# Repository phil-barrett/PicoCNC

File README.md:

# PicoCNC

## Now fully open source
I have released the full V1.55eth design files under the MIT open source license. Please post your usage and derivations in the [Discussions Section](https://github.com/phil-barrett/PicoCNC/discussions).

## older readme.
No longer available for purchase.

A breakout board that, along with grblHAL and a Rapsberry Pi Pico microcontroller, creates a powerful CNC motion controller for devices like routers, mills, lasers and lathes.  Using grblHAL, it forms the basis of a motion control system with advanced features.

[System builder's Resources](https://www.grbl.org/resources)

[User Manual](https://github.com/phil-barrett/PicoCNC/blob/main/PicoCNC%20User%20Manual.pdf)

Key features of the PicoCNC board.
* Supports up to 4 Axes via Screw Terminal and Pin Header.
* Spindle control.
  - PWM (5V).
  - Direction (5V).
  - 0-10V.
  - 12V PWM supported (via open collector output).
* Limit Switches for each axis.
  - Supports switches or powered proximity sensors.​
  - 12V for better EMI immunity.
  - Separate power input for full isolation
  - Opto-isolated
* Relay support
  - Directly drive up to 7 relay coils via open collector outputs.​
  - Relay Coil voltage selectable between +5V or +12V.
  - Drive up to 11 SSR or Logic Level relays.
* Isolated standard Grbl input controls: Cycle Start, Feed Hold, EStop and Safety Door.​ Opto-Isolated.
* Opto-Isolated Probe input.
* Supports both Pico and Pico W.
* Comunications.
  - USB (via Pico and Pico W)
  - WiFi (via Pico W)
  - Ethernet (via Wiz850io Ethernet Module)
* Micro SD Card socket.  Allows storage of GCode programs.  GCode programs may be run from the SD Card.
* Dust Collection support.
  - Dust Collection relay and TTL output ganged to Spindle. 
  - Header for a switch to manually run Dust Collector.
* Flexible power input.  Two 12V sections, one for Stepper/Servo output, relays and spindle control, one for isolated limit, probe and control inputs. The two sections may be joined for the budget conscious builder. On board 5V generation.​
* LED indicators for 12V inputs, +5V​​ and spindle active.
* Open collector outputs allow adding pull-up resistors on the board.
* Expansion headers for I2C, SPI and UART.  UART 3.3V/5V translation supported.
* Powered by open source software - grblHAL.

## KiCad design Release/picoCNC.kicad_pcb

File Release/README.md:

## MIT License release of PicoCNC design files.

Copyright (c) 2023, 2025 Phillip L. Barrett

Permission is hereby granted, free of charge, to any person obtaining a copy
of this software and associated documentation files (the "Software"), to deal
in the Software without restriction, including without limitation the rights
to use, copy, modify, merge, publish, distribute, sublicense, and/or sell
copies of the Software, and to permit persons to whom the Software is
furnished to do so, subject to the following conditions:

The above copyright notice and this permission notice shall be included in all
copies or substantial portions of the Software.

THE SOFTWARE IS PROVIDED "AS IS", WITHOUT WARRANTY OF ANY KIND, EXPRESS OR
IMPLIED, INCLUDING BUT NOT LIMITED TO THE WARRANTIES OF MERCHANTABILITY,
FITNESS FOR A PARTICULAR PURPOSE AND NONINFRINGEMENT. IN NO EVENT SHALL THE
AUTHORS OR COPYRIGHT HOLDERS BE LIABLE FOR ANY CLAIM, DAMAGES OR OTHER
LIABILITY, WHETHER IN AN ACTION OF CONTRACT, TORT OR OTHERWISE, ARISING FROM,
OUT OF OR IN CONNECTION WITH THE SOFTWARE OR THE USE OR OTHER DEALINGS IN THE
SOFTWARE.

## Usage Notes

### KiCAD Files
These were created with KiCAD V8.0

They are released with the intent of using JLCPCB to manufacture the PCB and 
assemble them into a working circuit board. The directory production/ includes full gerbers (PicoU4XBB.zip), 
Bill of Materials including JLCPCB library part numbers (bom,.csv) and Centroid PnP (positions.csv).

### KiCAD plugins required
To create JLCPCB files after modifying the design, you will need the Fabrication Toolkit plugin. It is 
available in the KICAD Plugin and Content Manager.

### JLCPCB Library part numbers
These were current as of June 2025.  You may need to change due to out of stock parts.

## Questions, reports, suggestions

Please use the [Discussions section](https://github.com/phil-barrett/PicoCNC/discussions/34) to ask questions, report your progress or make suggestions.

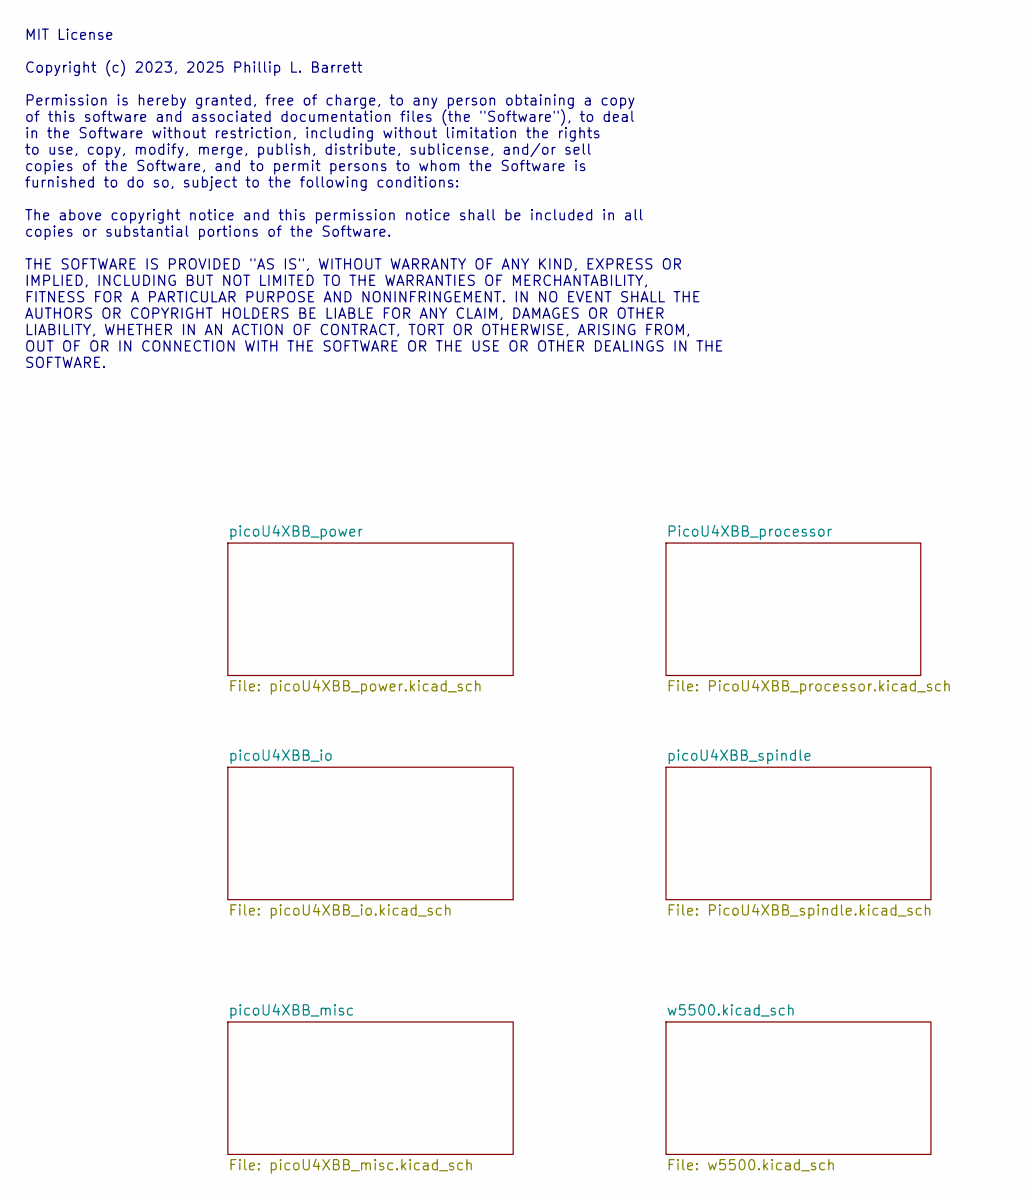
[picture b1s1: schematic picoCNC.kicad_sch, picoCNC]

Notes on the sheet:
MIT License Copyright (c) 2023, 2025 Phillip L. Barrett Permission is hereby granted, free of charge, to any person obtaining a copy of this software and associated documentation files (the "Software"), to deal in the Software without restriction, including without limitation the rights to use, cop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

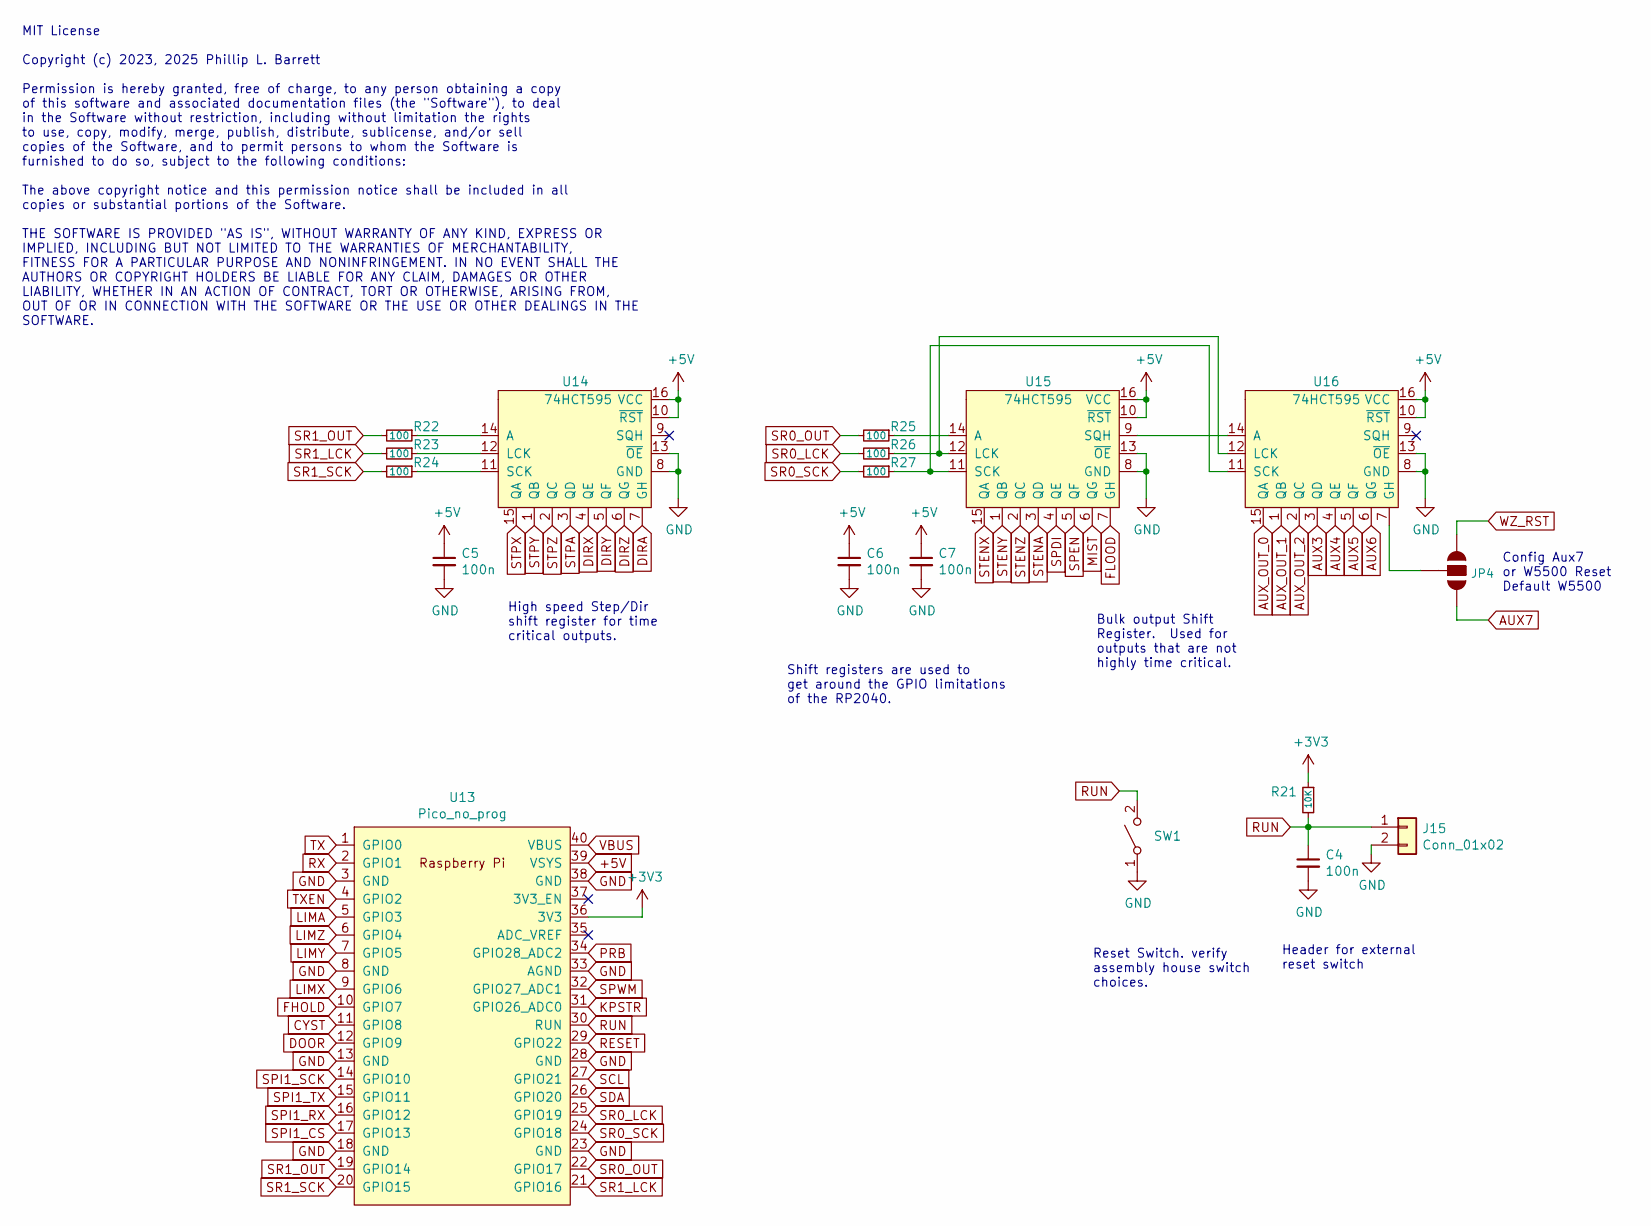
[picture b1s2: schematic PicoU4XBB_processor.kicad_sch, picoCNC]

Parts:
C4, C5, C6, C7: 100n; C_0805_2012Metric; LCSC C49678
J15: Conn_01x02; 1X02
JP4: JUMPER-SMT_3_NO_NO-SILK; SolderJumper-3_P1.3mm_Bridged12_Pad1.0x1.5mm
R21: 10K; R_0603_1608Metric; LCSC C25804
R22, R23, R24, R25, R26, R27: 100; R_0603_1608Metric; LCSC C22775
SW1: SW_SPST; TA-1088R-02026; LCSC C455280
U13: Pico_no_prog; RaspBerry_PI_Pico_no_prog
U14, U15, U16: 74HCT595; HTSSOP-16_4.4x5mm_P0.65; LCSC C460504

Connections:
+5V: C5.1, C6.1, C7.1, U13.39 (VSYS), U14.10 (~RST), U14.16 (VCC), U15.10 (~RST), U15.16 (VCC), U16.10 (~RST), U16.16 (VCC); also elsewhere on the board
AUX0: U16.15 (QA); also elsewhere on the board
AUX1: U16.1 (QB); also elsewhere on the board
AUX2: U16.2 (QC); also elsewhere on the board
AUX3: U16.3 (QD); also elsewhere on the board
AUX4: U16.4 (QE); also elsewhere on the board
AUX5: U16.5 (QF); also elsewhere on the board
AUX6: U16.6 (QG); also elsewhere on the board
AUX7: JP4.3; also elsewhere on the board
CYST: U13.11 (GPIO8); also elsewhere on the board
DIRA: U14.7 (GH); also elsewhere on the board
DIRX: U14.4 (QE); also elsewhere on the board
DIRY: U14.5 (QF); also elsewhere on the board
DIRZ: U14.6 (QG); also elsewhere on the board
DOOR: U13.12 (GPIO9); also elsewhere on the board
FHOLD: U13.10 (GPIO7); also elsewhere on the board
FLOOD: U15.7 (GH); also elsewhere on the board
GND: C4.2, C5.2, C6.2, C7.2, J15.2, SW1.1 (A), U13.3 (GND), U13.8 (GND), U13.13 (GND), U13.18 (GND), U13.23 (GND), U13.28 (GND), U13.33 (AGND), U13.38 (GND), U14.8 (GND), U14.13 (~OE), U15.8 (GND), U15.13 (~OE), U16.8 (GND), U16.13 (~OE); also elsewhere on the board
KPSTR: U13.31 (GPIO26_ADC0); also elsewhere on the board
LIMA: U13.5 (GPIO3); also elsewhere on the board
LIMX: U13.9 (GPIO6); also elsewhere on the board
LIMY: U13.7 (GPIO5); also elsewhere on the board
LIMZ: U13.6 (GPIO4); also elsewhere on the board
MIST: U15.6 (QG); also elsewhere on the board
unnamed: R22.1, U14.14 (A)
unnamed: R23.1, U14.12 (LCK)
unnamed: R24.1, U14.11 (SCK)
unnamed: R25.1, U15.14 (A)
unnamed: R26.1, U15.12 (LCK), U16.12 (LCK)
unnamed: R27.1, U15.11 (SCK), U16.11 (SCK)
unnamed: U15.9 (SQH), U16.14 (A)
unnamed: JP4.2, U16.7 (GH)
PRB: U13.34 (GPIO28_ADC2); also elsewhere on the board
RESET: U13.29 (GPIO22); also elsewhere on the board
RUN: C4.1, J15.1, R21.2, SW1.2 (B), U13.30 (RUN)
RX: U13.2 (GPIO1); also elsewhere on the board
SCL: U13.27 (GPIO21); also elsewhere on the board
SDA: U13.26 (GPIO20); also elsewhere on the board
SPDI: U15.4 (QE); also elsewhere on the board
SPEN: U15.5 (QF); also elsewhere on the board
SPI1_CS: U13.17 (GPIO13); also elsewhere on the board
SPI1_RX: U13.16 (GPIO12); also elsewhere on the board
SPI1_SCK: U13.14 (GPIO10); also elsewhere on the board
SPI1_TX: U13.15 (GPIO11); also elsewhere on the board
SPWM: U13.32 (GPIO27_ADC1); also elsewhere on the board
SR0_LCK: R26.2, U13.25 (GPIO19)
SR0_OUT: R25.2, U13.22 (GPIO17)
SR0_SCK: R27.2, U13.24 (GPIO18)
SR1_LCK: R23.2, U13.21 (GPIO16)
SR1_OUT: R22.2, U13.19 (GPIO14)
SR1_SCK: R24.2, U13.20 (GPIO15)
STENA: U15.3 (QD); also elsewhere on the board
STENX: U15.15 (QA); also elsewhere on the board
STENY: U15.1 (QB); also elsewhere on the board
STENZ: U15.2 (QC); also elsewhere on the board
STPA: U14.3 (QD); also elsewhere on the board
STPX: U14.15 (QA); also elsewhere on the board
STPY: U14.1 (QB); also elsewhere on the board
STPZ: U14.2 (QC); also elsewhere on the board
TX: U13.1 (GPIO0); also elsewhere on the board
TXEN: U13.4 (GPIO2); also elsewhere on the board
VBUS: U13.40 (VBUS); also elsewhere on the board
WZ_RST: JP4.1; also elsewhere on the board

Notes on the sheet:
Config Aux7 or W5500 Reset Default W5500
Reset Switch. verify assembly house switch choices.
Shift registers are used to get around the GPIO limitations of the RP2040.
MIT License Copyright (c) 2023, 2025 Phillip L. Barrett Permission is hereby granted, free of charge, to any person obtaining a copy of this software and associated documentation files (the "Software"), to deal in the Software without restriction, including without limitation the rights to use, cop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
Bulk output Shift Register. Used for outputs that are not highly time critical.
High speed Step/Dir shift register for time critical outputs.
Header for external reset switch

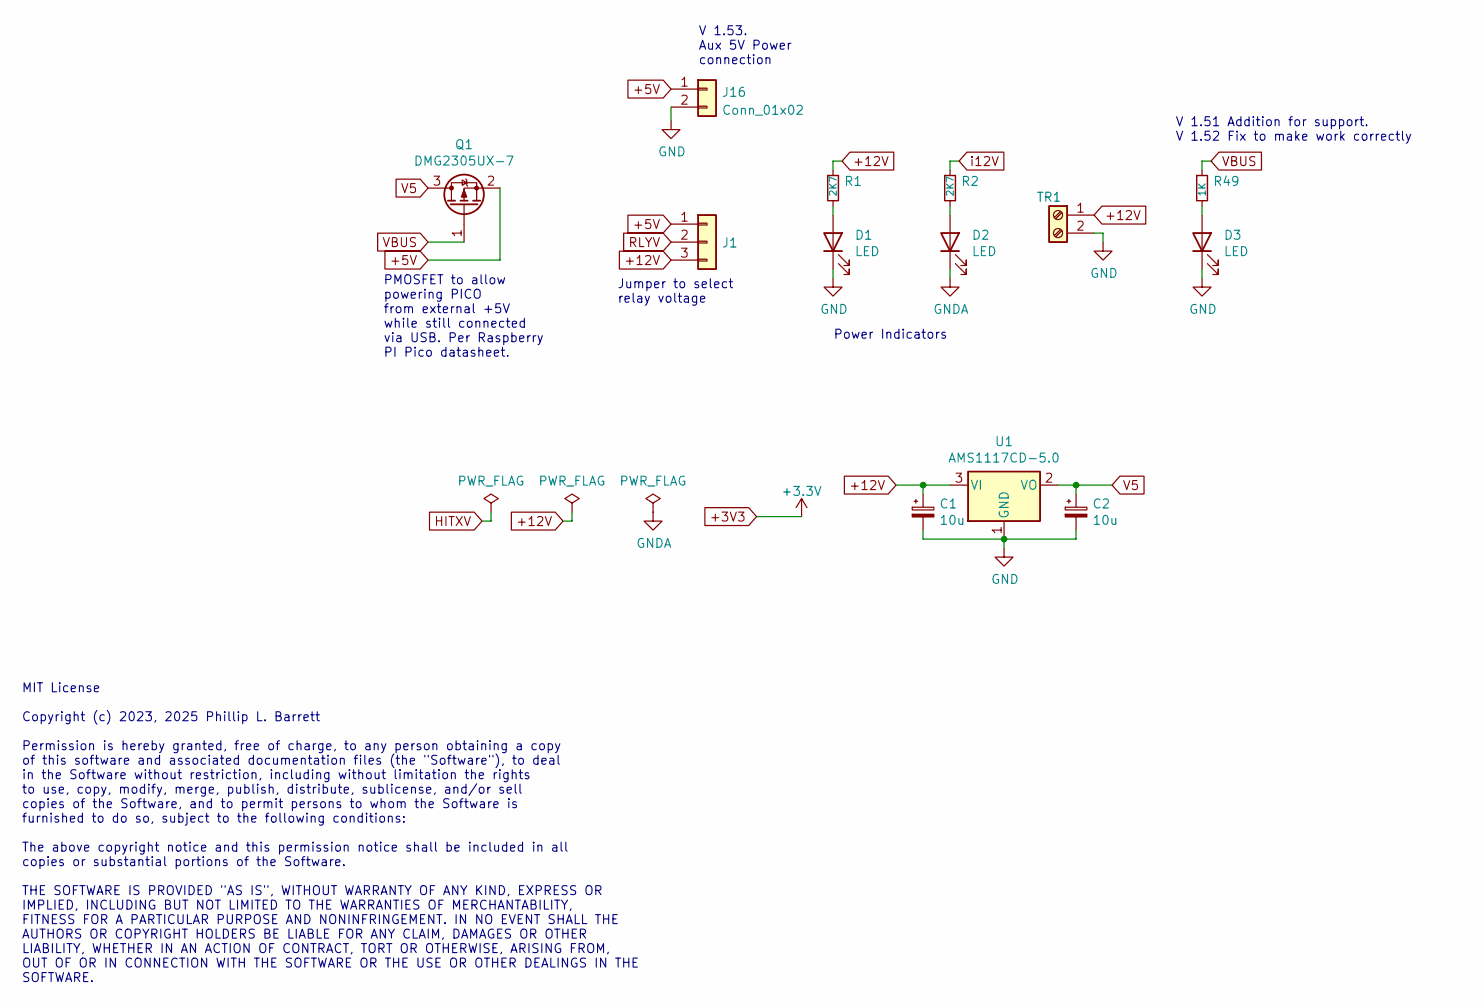
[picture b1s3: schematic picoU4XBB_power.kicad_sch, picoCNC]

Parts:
C1, C2: 10u; C_0805_2012Metric; LCSC C15850
D1, D2, D3: LED; LED_0805_2012Metric; LCSC C2297
J1: Conn_01x03; 1X03
J16: Conn_01x02; 1X02
Q1: DMG2305UX-7; SOT-23-rct; LCSC C150470
R1, R2: 2K7; R_0603_1608Metric; LCSC C13167
R49: 1K; R_0603_1608Metric; LCSC C21190
TR1: pterm3.5-2; T35-2-5milh; LCSC C409115
U1: AMS1117CD-5.0; SOT-223-3_TabPin2; LCSC C277893

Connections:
+5V: J1.1, J16.1, Q1.2 (S); also elsewhere on the board
+12V: C1.1, J1.3, R1.1, TR1.1, U1.3 (VI); also elsewhere on the board
GND: C1.2, C2.2, D1.1 (K), D3.1 (K), J16.2, TR1.2, U1.1 (GND); also elsewhere on the board
GNDA: D2.1 (K); also elsewhere on the board
unnamed: D1.2 (A), R1.2
unnamed: D2.2 (A), R2.2
unnamed: D3.2 (A), R49.2
RLYV: J1.2; also elsewhere on the board
V5: C2.1, Q1.3 (D), U1.2 (VO)
VBUS: Q1.1 (G), R49.1; also elsewhere on the board
i12V: R2.1; also elsewhere on the board

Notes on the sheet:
V 1.53. Aux 5V Power connection
Power Indicators
Jumper to select relay voltage
V 1.51 Addition for support. V 1.52 Fix to make work correctly
MIT License Copyright (c) 2023, 2025 Phillip L. Barrett Permission is hereby granted, free of charge, to any person obtaining a copy of this software and associated documentation files (the "Software"), to deal in the Software without restriction, including without limitation the rights to use, cop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
PMOSFET to allow powering PICO from external +5V while still connected via USB. Per Raspberry PI Pico datasheet.

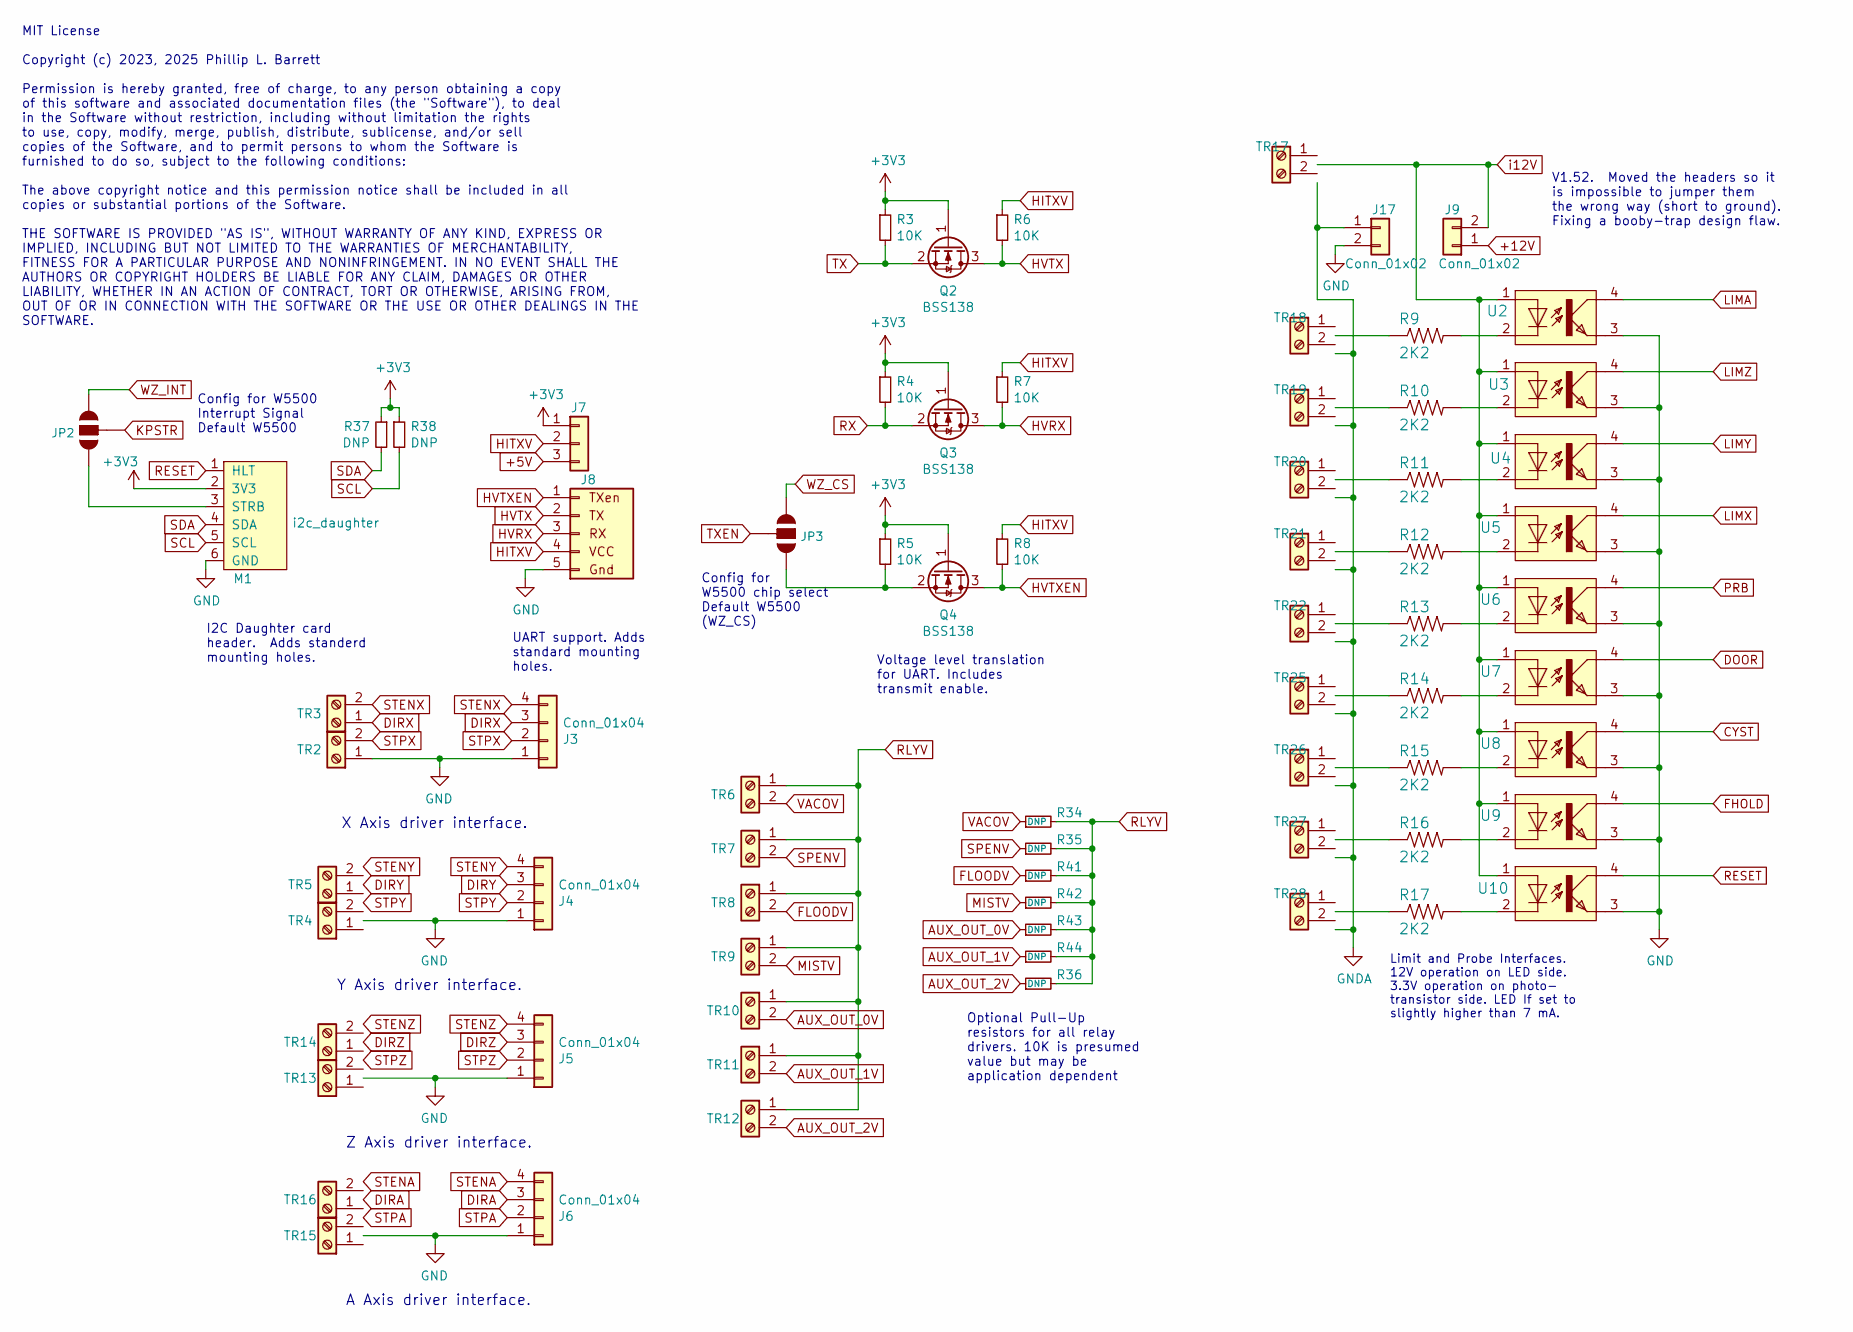
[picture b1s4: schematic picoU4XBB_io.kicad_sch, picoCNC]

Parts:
J3, J4, J5, J6: Conn_01x04; 1X04
J7: Conn_01x03; 1X03
J8: async_daughter; Serial_header_mountin_holes
J9: Conn_01x02; 1X02-1mm
J17: Conn_01x02; 1X02
JP2, JP3: JUMPER-SMT_3_NO_NO-SILK; SolderJumper-3_P1.3mm_Bridged12_Pad1.0x1.5mm
M1: i2c_daughter; I2C_Header
Q2, Q3, Q4: BSS138; SOT-23-rct; LCSC C40912
R3, R4, R5, R6, R7, R8: 10K; R_0603_1608Metric; LCSC C25804
R9, R10, R11, R12, R13, R14, R15, R16, R17: 2K2; R_0603_1608Metric; LCSC C4190
R34, R35, R36, R41, R42, R43, R44: DNP; R_0805_2012Metric_Pad1.20x1.40mm_HandSolder; LCSC DNP
R37, R38: DNP; R_0805_2012Metric; LCSC C17520
TR2, TR3, TR4, TR5, TR6, TR7, TR8, TR9, TR10, TR11, TR12, TR13, TR14, TR15, TR16, TR17, TR18, TR19, TR20, TR21, TR22, TR25, TR26, TR27, TR28: pterm3.5-2; T35-2-5milh; LCSC C409115
U2, U3, U4, U5, U6, U7, U8, U9, U10: EL3H7-G; LCSC C92243

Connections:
+5V: J7.3; also elsewhere on the board
+12V: J9.1; also elsewhere on the board
AUX0V: R43.1, TR10.2; also elsewhere on the board
AUX1V: R44.1, TR11.2; also elsewhere on the board
AUX2V: R36.1, TR12.2; also elsewhere on the board
CYST: U8.4 (COL); also elsewhere on the board
DIRA: J6.3, TR16.1; also elsewhere on the board
DIRX: J3.3, TR3.1; also elsewhere on the board
DIRY: J4.3, TR5.1; also elsewhere on the board
DIRZ: J5.3, TR14.1; also elsewhere on the board
DOOR: U7.4 (COL); also elsewhere on the board
FHOLD: U9.4 (COL); also elsewhere on the board
FLOODV: R41.1, TR8.2; also elsewhere on the board
GND: J3.1, J4.1, J5.1, J6.1, J8.5 (Gnd), J17.2, M1.6 (GND), TR2.1, TR4.1, TR13.1, TR15.1, U2.3 (EMIT), U3.3 (EMIT), U4.3 (EMIT), U5.3 (EMIT), U6.3 (EMIT), U7.3 (EMIT), U8.3 (EMIT), U9.3 (EMIT), U10.3 (EMIT); also elsewhere on the board
GNDA: J17.1, TR17.2, TR18.2, TR19.2, TR20.2, TR21.2, TR22.2, TR25.2, TR26.2, TR27.2, TR28.2; also elsewhere on the board
HITXV: J7.2, J8.4 (VCC), R6.1, R7.1, R8.1
HVRX: J8.3 (RX), Q3.3 (D), R7.2
HVTX: J8.2 (TX), Q2.3 (D), R6.2
HVTXEN: J8.1 (TXen), Q4.3 (D), R8.2
KPSTR: JP2.2; also elsewhere on the board
LIMA: U2.4 (COL); also elsewhere on the board
LIMX: U5.4 (COL); also elsewhere on the board
LIMY: U4.4 (COL); also elsewhere on the board
LIMZ: U3.4 (COL); also elsewhere on the board
MISTV: R42.1, TR9.2; also elsewhere on the board
unnamed: JP2.3, M1.3 (STRB)
unnamed: JP3.3, Q4.2 (S), R5.2
unnamed: R9.1, TR18.1
unnamed: R10.1, TR19.1
unnamed: R11.1, TR20.1
unnamed: R12.1, TR21.1
unnamed: R13.1, TR22.1
unnamed: R14.1, TR25.1
unnamed: R15.1, TR26.1
unnamed: R16.1, TR27.1
unnamed: R17.1, TR28.1
unnamed: R9.2, U2.2 (C)
unnamed: R10.2, U3.2 (C)
unnamed: R11.2, U4.2 (C)
unnamed: R12.2, U5.2 (C)
unnamed: R13.2, U6.2 (C)
unnamed: R14.2, U7.2 (C)
unnamed: R15.2, U8.2 (C)
unnamed: R16.2, U9.2 (C)
unnamed: R17.2, U10.2 (C)
PRB: U6.4 (COL); also elsewhere on the board
RESET: M1.1 (HLT), U10.4 (COL); also elsewhere on the board
RLYV: R34.2, R35.2, R36.2, R41.2, R42.2, R43.2, R44.2, TR6.1, TR7.1, TR8.1, TR9.1, TR10.1, TR11.1, TR12.1; also elsewhere on the board
RX: Q3.2 (S), R4.2; also elsewhere on the board
SCL: M1.5 (SCL), R38.2; also elsewhere on the board
SDA: M1.4 (SDA), R37.2; also elsewhere on the board
SPENV: R35.1, TR7.2; also elsewhere on the board
STENA: J6.4, TR16.2; also elsewhere on the board
STENX: J3.4, TR3.2; also elsewhere on the board
STENY: J4.4, TR5.2; also elsewhere on the board
STENZ: J5.4, TR14.2; also elsewhere on the board
STPA: J6.2, TR15.2; also elsewhere on the board
STPX: J3.2, TR2.2; also elsewhere on the board
STPY: J4.2, TR4.2; also elsewhere on the board
STPZ: J5.2, TR13.2; also elsewhere on the board
TX: Q2.2 (S), R3.2; also elsewhere on the board
TXEN: JP3.2; also elsewhere on the board
VACOV: R34.1, TR6.2; also elsewhere on the board
WZ_CS: JP3.1; also elsewhere on the board
WZ_INT: JP2.1; also elsewhere on the board
i12V: J9.2, TR17.1, U2.1 (A), U3.1 (A), U4.1 (A), U5.1 (A), U6.1 (A), U7.1 (A), U8.1 (A), U9.1 (A), U10.1 (A); also elsewhere on the board

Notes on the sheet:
X Axis driver interface.
Z Axis driver interface.
UART support. Adds standard mounting holes.
Limit and Probe Interfaces. 12V operation on LED side. 3.3V operation on photo- transistor side. LED If set to slightly higher than 7 mA.
MIT License Copyright (c) 2023, 2025 Phillip L. Barrett Permission is hereby granted, free of charge, to any person obtaining a copy of this software and associated documentation files (the "Software"), to deal in the Software without restriction, including without limitation the rights to use, cop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
Voltage level translation for UART. Includes transmit enable.
Optional Pull-Up resistors for all relay drivers. 10K is presumed value but may be application dependent
A Axis driver interface.
Y Axis driver interface.
I2C Daughter card header. Adds standerd mounting holes.
Config for W5500 chip select Default W5500 (WZ_CS)
V1.52. Moved the headers so it is impossible to jumper them the wrong way (short to ground). Fixing a booby-trap design flaw.
Config for W5500 Interrupt Signal Default W5500

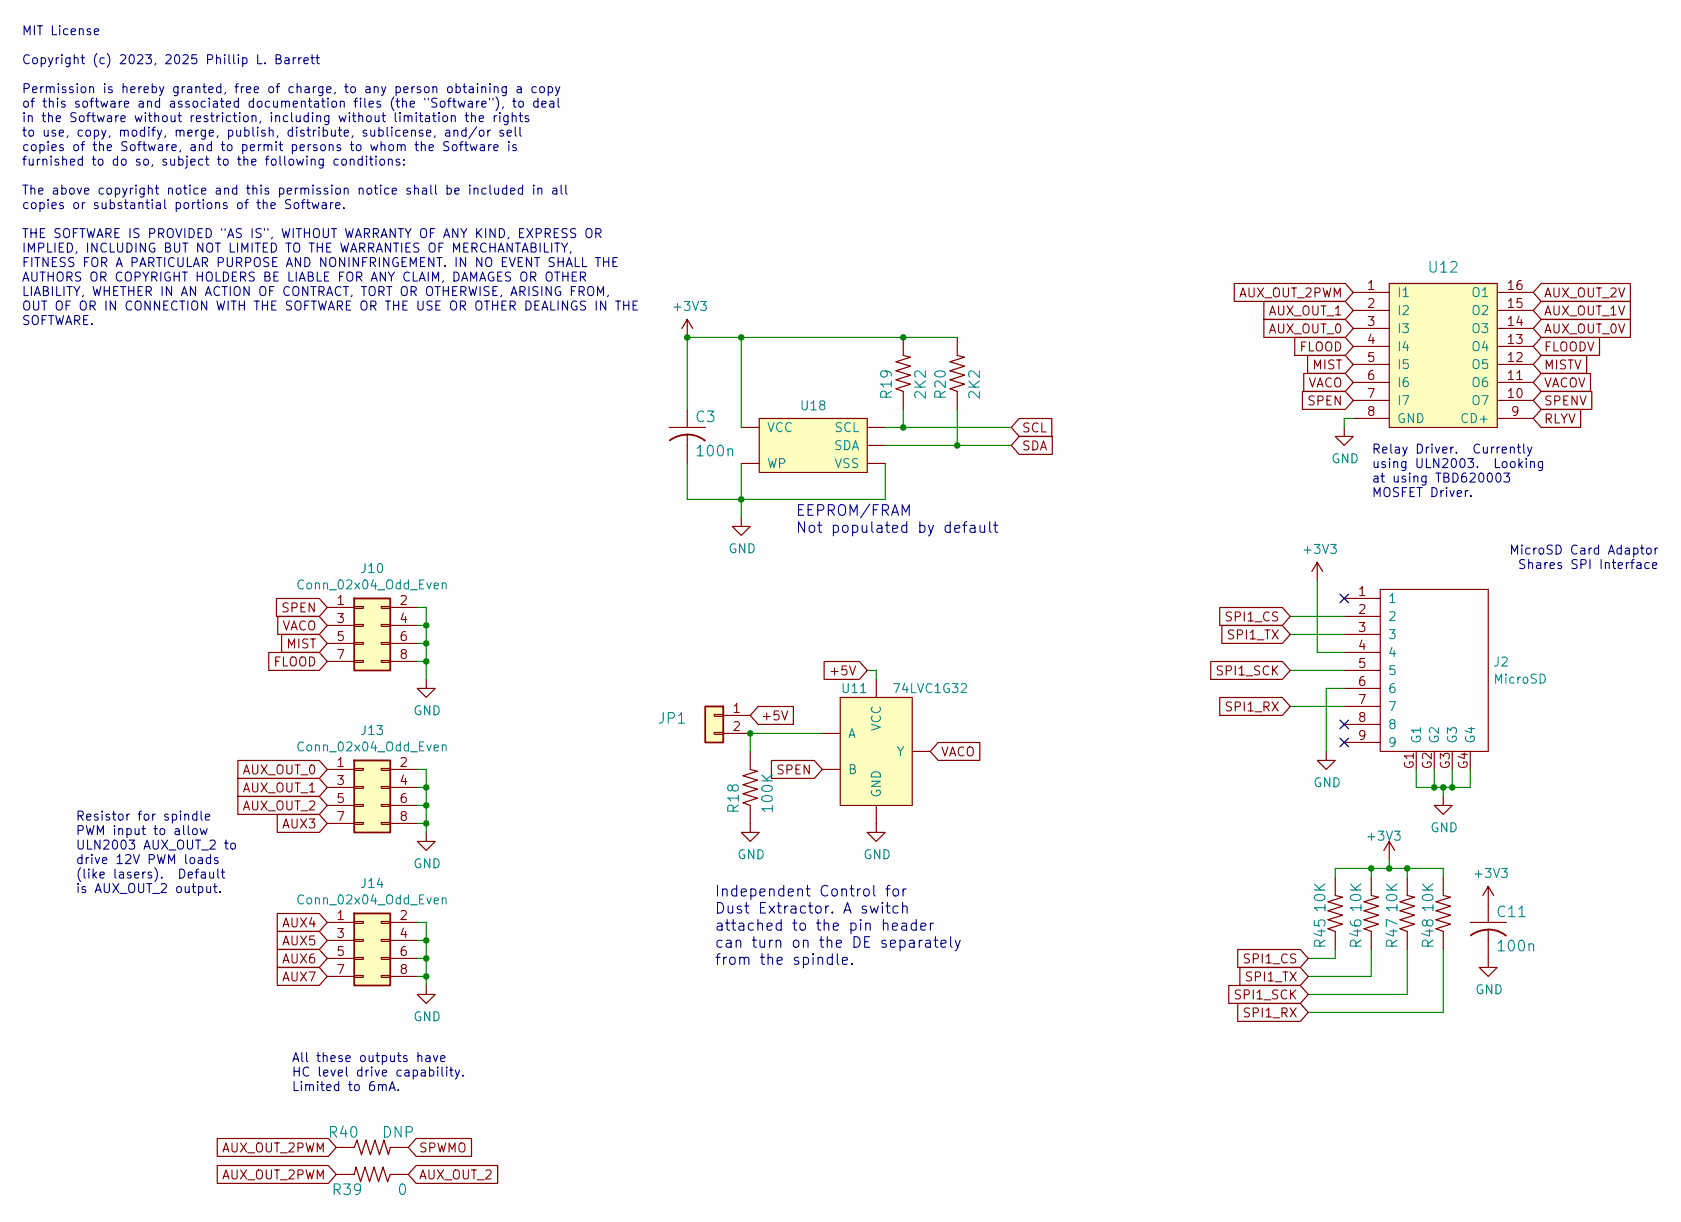
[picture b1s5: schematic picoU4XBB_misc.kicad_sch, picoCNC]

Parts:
C3, C11: 100n; C_0805_2012Metric; LCSC C49678
J2: MicroSD
J10, J13, J14: Conn_02x04_Odd_Even; 2X04
JP1: PINHD-1X2; 1X02; LCSC C358684
R18: 100K; R_0603_1608Metric; LCSC C25803
R19, R20: 2K2; R_0603_1608Metric; LCSC C4190
R39: 0; R_0805_2012Metric; LCSC C17477
R40: DNP; R_0805_2012Metric; LCSC C17407
R45, R46, R47, R48: 10K; R_0603_1608Metric; LCSC C25804
U11: 74LVC1G32; SOT-353_SC-70-5; LCSC C460530
U12: ULN2003AD; SO16; LCSC C7512
U18: FM24CLxxx; SO08

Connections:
+5V: JP1.1, U11.5 (VCC); also elsewhere on the board
AUX0: J13.1, U12.3 (I3); also elsewhere on the board
AUX0V: U12.14 (O3); also elsewhere on the board
AUX1: J13.3, U12.2 (I2); also elsewhere on the board
AUX1V: U12.15 (O2); also elsewhere on the board
AUX2: J13.5, R39.1; also elsewhere on the board
AUX2PWM: R39.2, R40.1, U12.1 (I1)
AUX2V: U12.16 (O1); also elsewhere on the board
AUX3: J13.7; also elsewhere on the board
AUX4: J14.1; also elsewhere on the board
AUX5: J14.3; also elsewhere on the board
AUX6: J14.5; also elsewhere on the board
AUX7: J14.7; also elsewhere on the board
FLOOD: J10.7, U12.4 (I4); also elsewhere on the board
FLOODV: U12.13 (O4); also elsewhere on the board
GND: C3.2, C11.2, J2.6, J2.G1, J2.G2, J2.G3, J2.G4, J2.MP1, J2.MP2, J2.MP3, J2.MP4, J10.2, J10.4, J10.6, J10.8, J13.2, J13.4, J13.6, J13.8, J14.2, J14.4, J14.6, J14.8, R18.1, U11.3 (GND), U12.8 (GND), U18.4 (VSS), U18.7 (WP); also elsewhere on the board
MIST: J10.5, U12.5 (I5); also elsewhere on the board
MISTV: U12.12 (O5); also elsewhere on the board
unnamed: JP1.2, R18.2, U11.1 (A)
RLYV: U12.9 (CD+); also elsewhere on the board
SCL: R19.1, U18.6 (SCL); also elsewhere on the board
SDA: R20.1, U18.5 (SDA); also elsewhere on the board
SPEN: J10.1, U11.2 (B), U12.7 (I7); also elsewhere on the board
SPENV: U12.10 (O7); also elsewhere on the board
SPI1_CS: J2.2, R45.1; also elsewhere on the board
SPI1_RX: J2.7, R48.1; also elsewhere on the board
SPI1_SCK: J2.5, R47.1; also elsewhere on the board
SPI1_TX: J2.3, R46.1; also elsewhere on the board
SPWMO: R40.2; also elsewhere on the board
VACO: J10.3, U11.4 (Y), U12.6 (I6)
VACOV: U12.11 (O6); also elsewhere on the board

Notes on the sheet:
MicroSD Card Adaptor Shares SPI Interface
All these outputs have HC level drive capability. Limited to 6mA.
EEPROM/FRAM Not populated by default
Resistor for spindle PWM input to allow ULN2003 AUX_OUT_2 to drive 12V PWM loads (like lasers). Default is AUX_OUT_2 output.
Relay Driver. Currently using ULN2003. Looking at using TBD620003 MOSFET Driver.
MIT License Copyright (c) 2023, 2025 Phillip L. Barrett Permission is hereby granted, free of charge, to any person obtaining a copy of this software and associated documentation files (the "Software"), to deal in the Software without restriction, including without limitation the rights to use, cop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
Independent Control for Dust Extractor. A switch attached to the pin header can turn on the DE separately from the spindle.

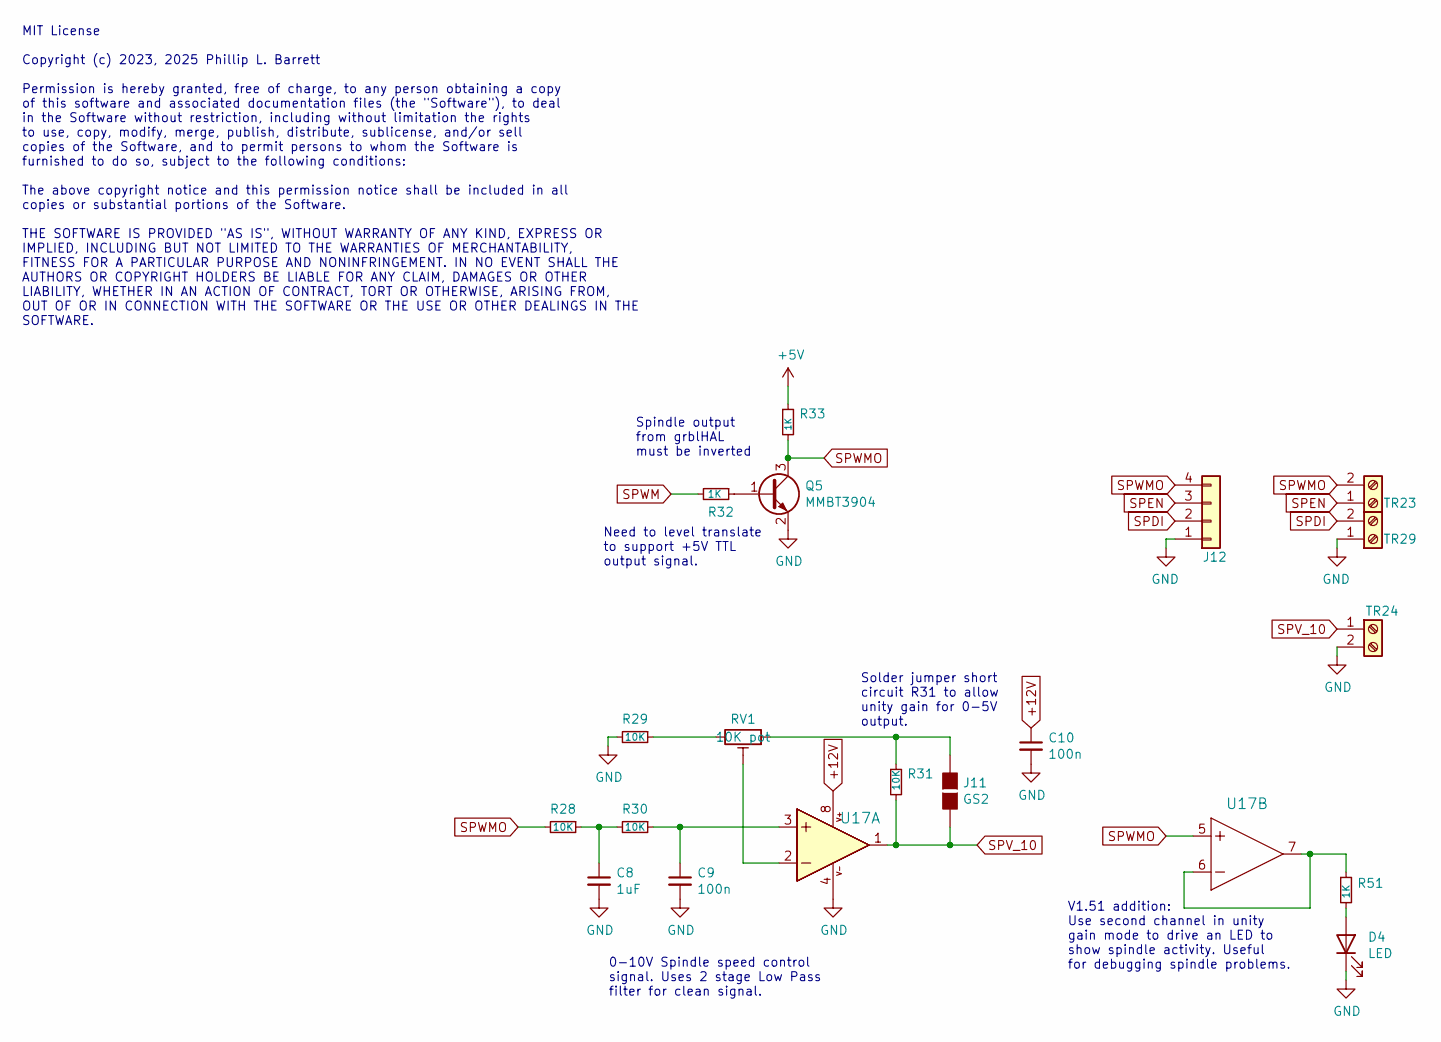
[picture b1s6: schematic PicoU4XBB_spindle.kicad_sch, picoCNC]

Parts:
C8: 1uF; C_0805_2012Metric; LCSC C28323
C9, C10: 100n; C_0805_2012Metric; LCSC C49678
D4: LED; LED_0805_2012Metric; LCSC C2297
J11: GS2; SolderJumper-2_P1.3mm_Open_RoundedPad1.0x1.5mm
J12: Conn_01x04; 1X04
Q5: MMBT3904; SOT-23-rct; LCSC C20526
R28, R29, R30, R31: 10K; R_0603_1608Metric; LCSC C25804
R32, R33, R51: 1K; R_0603_1608Metric; LCSC C21190
RV1: 10K pot; RM065-trimmer; LCSC C5205021
TR23, TR24, TR29: pterm3.5-2; T35-2-5milh; LCSC C409115
U17: LM358D; SO08; LCSC C2683482

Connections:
+5V: R33.1; also elsewhere on the board
+12V: C10.1, U17.8 (V+); also elsewhere on the board
GND: C8.2, C9.2, C10.2, D4.1 (K), J12.1, Q5.2 (E), R29.2, TR24.2, TR29.1, U17.4 (V-); also elsewhere on the board
unnamed: C8.1, R28.1, R30.2
unnamed: D4.2 (A), R51.2
unnamed: J11.1 (G1), R31.1, RV1.1
unnamed: Q5.1 (B), R32.1
unnamed: R29.1, RV1.3
unnamed: C9.1, R30.1, U17.3 (+IN)
unnamed: RV1.2, U17.2 (-IN)
unnamed: R51.1, U17.6 (-IN), U17.7 (OUT)
SPDI: J12.2, TR29.2; also elsewhere on the board
SPEN: J12.3, TR23.1; also elsewhere on the board
SPV_10: J11.2 (G2), R31.2, TR24.1, U17.1 (OUT)
SPWM: R32.2; also elsewhere on the board
SPWMO: J12.4, Q5.3 (C), R28.2, R33.2, TR23.2, U17.5 (+IN); also elsewhere on the board

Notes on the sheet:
Need to level translate to support +5V TTL output signal.
Solder jumper short circuit R31 to allow unity gain for 0-5V output.
0-10V Spindle speed control signal. Uses 2 stage Low Pass filter for clean signal.
MIT License Copyright (c) 2023, 2025 Phillip L. Barrett Permission is hereby granted, free of charge, to any person obtaining a copy of this software and associated documentation files (the "Software"), to deal in the Software without restriction, including without limitation the rights to use, cop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
Spindle output from grblHAL must be inverted
V1.51 addition: Use second channel in unity gain mode to drive an LED to show spindle activity. Useful for debugging spindle problems.

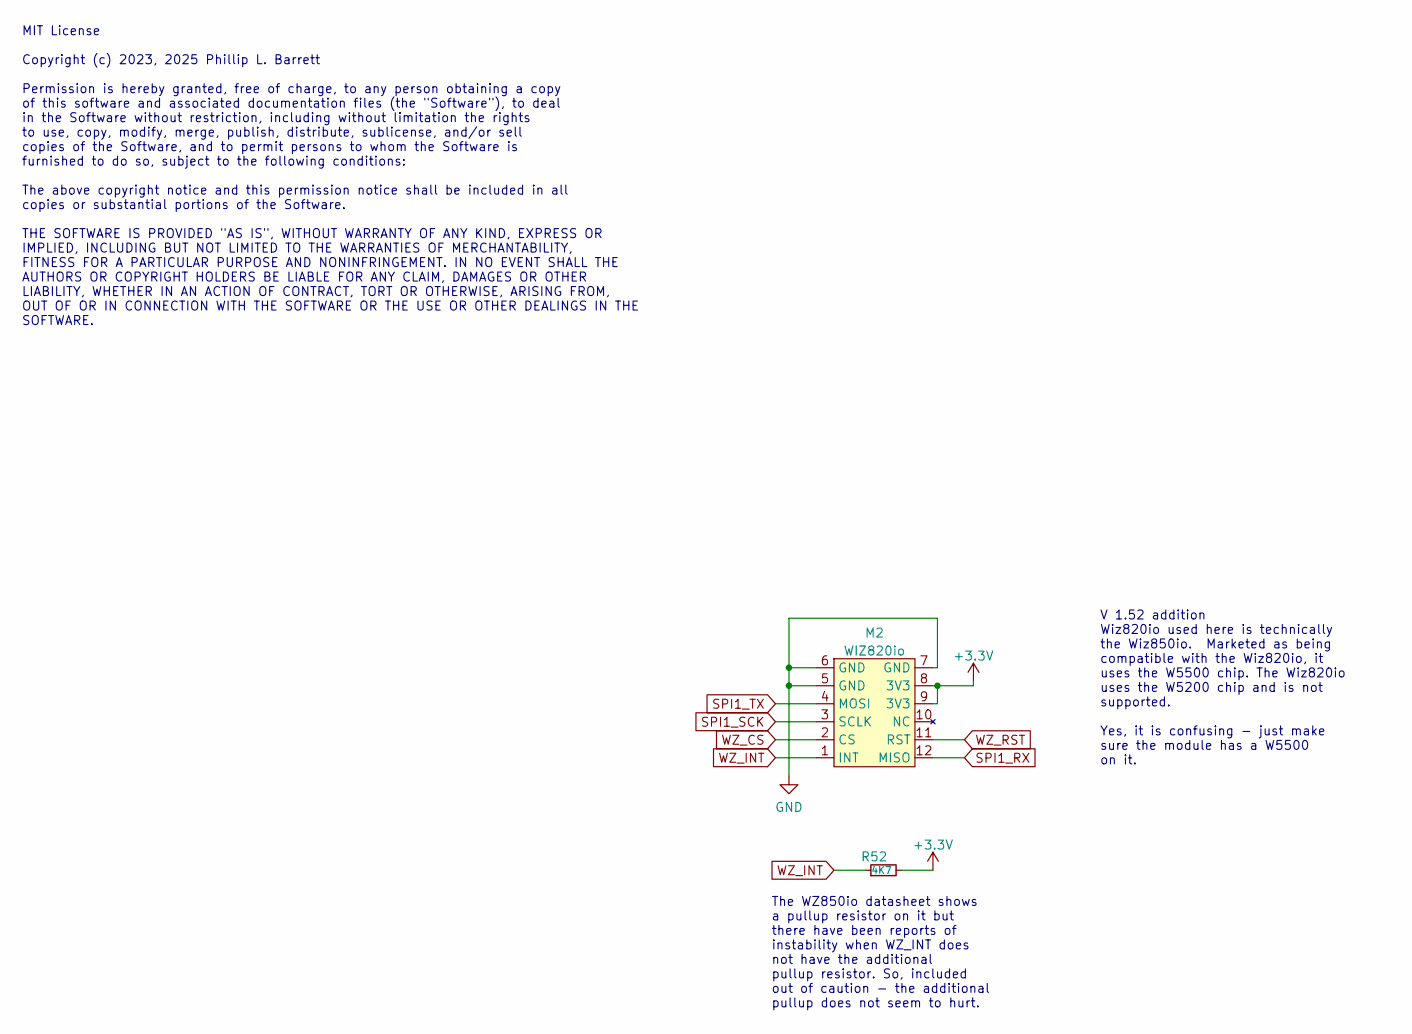
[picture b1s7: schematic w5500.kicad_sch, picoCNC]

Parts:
M2: WIZ820io; wiz820io
R52: 4K7; R_0603_1608Metric; LCSC C23162

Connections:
GND: M2.5 (GND), M2.6 (GND), M2.7 (GND); also elsewhere on the board
SPI1_RX: M2.12 (MISO); also elsewhere on the board
SPI1_SCK: M2.3 (SCLK); also elsewhere on the board
SPI1_TX: M2.4 (MOSI); also elsewhere on the board
WZ_CS: M2.2 (CS); also elsewhere on the board
WZ_INT: M2.1 (INT), R52.1; also elsewhere on the board
WZ_RST: M2.11 (RST); also elsewhere on the board

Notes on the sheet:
MIT License Copyright (c) 2023, 2025 Phillip L. Barrett Permission is hereby granted, free of charge, to any person obtaining a copy of this software and associated documentation files (the "Software"), to deal in the Software without restriction, including without limitation the rights to use, cop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
The WZ850io datasheet shows a pullup resistor on it but there have been reports of instability when WZ_INT does not have the additional pullup resistor. So, included out of caution - the additional pullup does not seem to hurt.
V 1.52 addition Wiz820io used here is technically the Wiz850io. Marketed as being compatible with the Wiz820io, it uses the W5500 chip. The Wiz820io uses the W5200 chip and is not supported. Yes, it is confusing - just make sure the module has a W5500 on it.

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

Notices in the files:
Release/picoCNC.kicad_pcb:
Copyright © 2023, 2025
Released under MIT License
